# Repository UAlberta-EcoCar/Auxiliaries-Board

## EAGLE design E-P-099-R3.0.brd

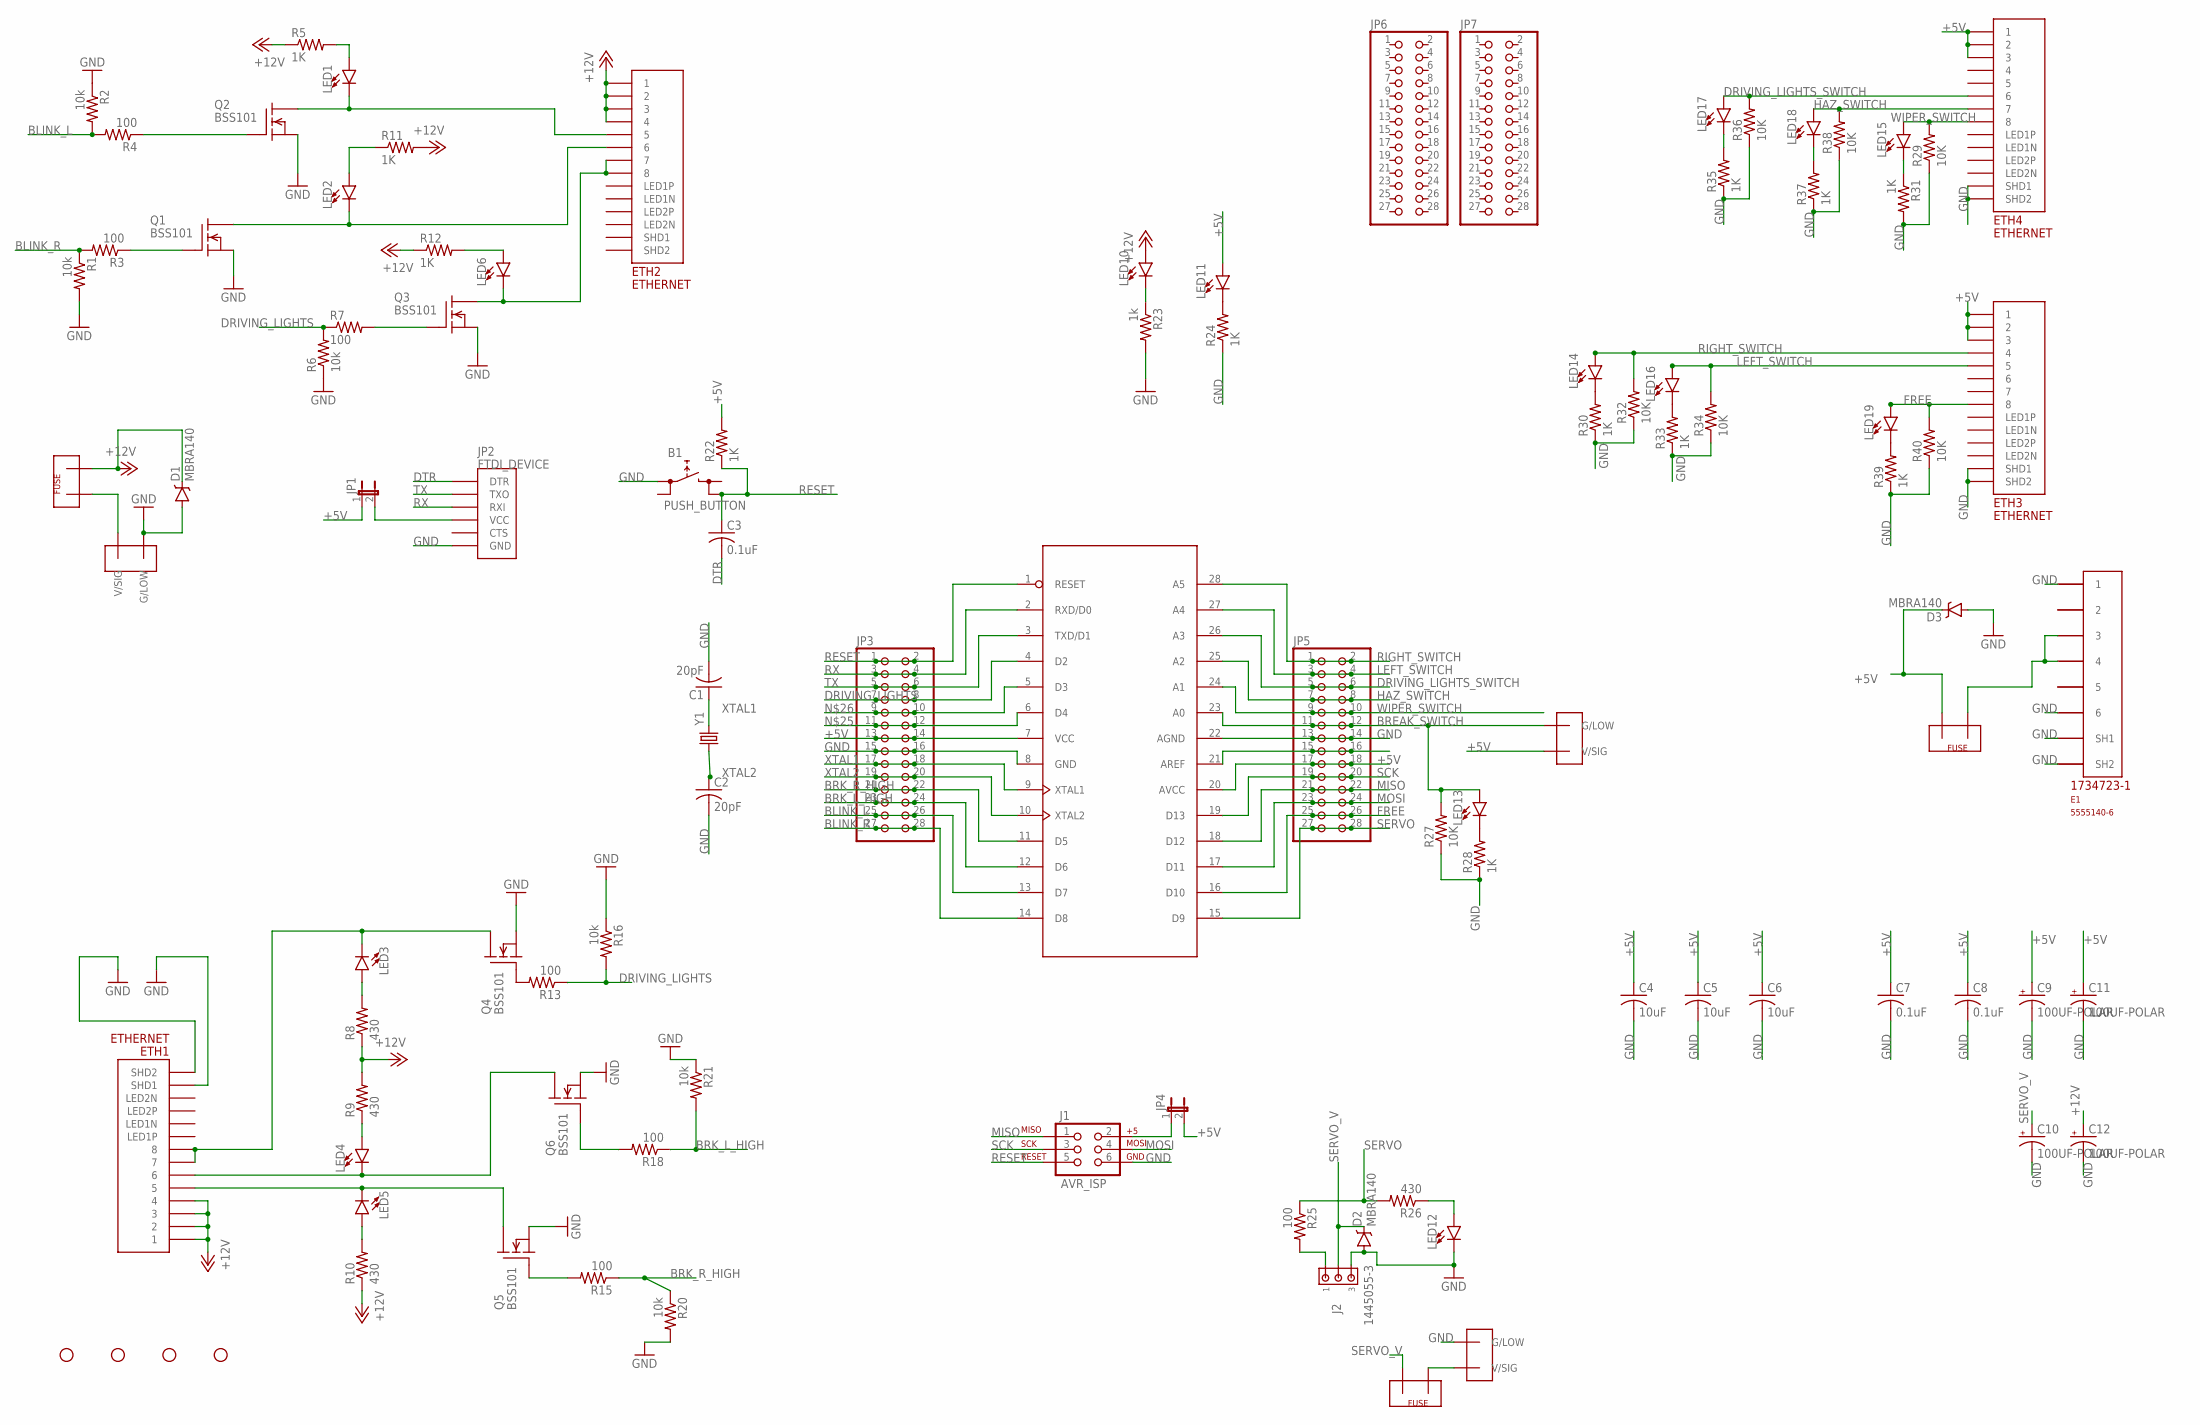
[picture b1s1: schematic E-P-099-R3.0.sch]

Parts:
AT1: ATMEGA328; DIP28-0.3IN
B1: PUSH_BUTTON; PUSHBUTTON
C1, C2: 20pF; C0805
C3, C7, C8: 0.1uF; C0805
C4, C5, C6: 10uF; C0805
C9, C10, C11, C12: 100UF-POLAR; EEU-FR1H101
D1, D2, D3: MBRA140; SMA-DIODE
E1: 5555140-6; 1734723-1_RJ11
ETH1, ETH2, ETH3, ETH4: ETHERNET; A122645-ND
F1, F2, F3: FUSEMINI-BLADE; MINI-BLADE-FUSE
J1: AVR_ISP; 2X3
J2: 1445055-3
JP1, JP4: JP1E; JP1
JP2: FTDI_DEVICE; FTDI_DEVICE_SIDE
JP3, JP5, JP6, JP7: PINHD-2X14; 2X14
LED1, LED2, LED3, LED4, LED5, LED6, LED10, LED11, LED12, LED13, LED14, LED15, LED16, LED17, LED18, LED19: LED0603; LED-0603
Q1, Q2, Q3, Q4, Q5, Q6: BSS101; TO92
R1, R2, R6, R16, R20, R21: 10k; 0805
R3, R4, R7, R13, R15, R18, R25: 100; 0805
R5, R11, R12, R22, R24, R28, R30, R31, R33, R35, R37, R39: 1K; 0805
R8, R9, R10, R26: 430; 0805
R23: 1k; 0805
R27, R29, R32, R34, R36, R38, R40: 10K; R0805
STANDOFF1, STANDOFF2, STANDOFF3, STANDOFF4: STAND-OFF
TE1, TE3: TE770966; 2X1-MATE-N-LOCK
TE2: SERVO_PWR; 2X1-MATE-N-LOCK
Y1: CRYSTALHC49US; HC49US

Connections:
+5V: AT1.7 (VCC), AT1.20 (AVCC), C4.1, C5.1, C6.1, C7.1, C8.1, C9.P (+), C11.P (+), D3.C, ETH3.P$1 (1), ETH3.P$2 (2), ETH3.P$3 (3), ETH4.P$1 (1), ETH4.P$2 (2), ETH4.P$3 (3), F3.OUT, JP1.1, JP3.13, JP3.14, JP4.2, JP5.17, JP5.18, LED11.A, R22.2, TE3.CIRCUIT1 (V/SIG)
+12V: C12.P (+), D1.C, ETH1.P$1 (1), ETH1.P$2 (2), ETH1.P$3 (3), ETH1.P$4 (4), ETH2.P$1 (1), ETH2.P$2 (2), ETH2.P$3 (3), ETH2.P$4 (4), F1.OUT, LED10.A, R5.1, R8.1, R9.2, R10.1, R11.2, R12.1
BLINK_L: AT1.13 (D7), JP3.25, JP3.26, R2.2, R4.2
BLINK_R: AT1.14 (D8), JP3.27, JP3.28, R1.1, R3.2
BREAK_SWITCH: AT1.23 (A0), JP5.11, JP5.12, LED13.A, R27.2, TE3.CIRCUIT2 (G/LOW)
BRK_L_HIGH: AT1.12 (D6), JP3.23, JP3.24, R18.1, R21.2
BRK_R_HIGH: AT1.11 (D5), JP3.21, JP3.22, R15.1, R20.1
DRIVING_LIGHTS: AT1.4 (D2), JP3.7, JP3.8, R6.2, R7.1, R13.1, R16.2
DRIVING_LIGHTS_SWITCH: AT1.26 (A3), ETH4.P$6 (6), JP5.5, JP5.6, LED17.A, R36.2
DTR: C3.2, JP2.P$1 (DTR)
FREE: AT1.16 (D10), ETH3.P$8 (8), JP5.25, JP5.26, LED19.A, R40.2
GND: AT1.8 (GND), AT1.22 (AGND), B1.L1 (L), C1.2, C2.2, C4.2, C5.2, C6.2, C7.2, C8.2, C9.G (-), C10.G (-), C11.G (-), C12.G (-), D1.A, D2.A, D3.A, E1.1, E1.6, E1.SH1, E1.SH2, ETH1.P$13 (SHD1), ETH1.P$14 (SHD2), ETH3.P$13 (SHD1), ETH3.P$14 (SHD2), ETH4.P$13 (SHD1), ETH4.P$14 (SHD2), J1.6, J2.3, JP2.P$6 (GND), JP3.15, JP3.16, JP5.13, JP5.14, LED12.C, Q1.1 (S), Q2.1 (S), Q3.1 (S), Q4.1 (S), Q5.1 (S), Q6.1 (S), R1.2, R2.1, R6.1, R16.1, R20.2, R21.1, R23.2, R24.1, R27.1, R28.1, R29.1, R30.1, R31.2, R32.1, R33.1, R34.1, R35.1, R36.1, R37.1, R38.1, R39.1, R40.1, TE1.CIRCUIT2 (G/LOW), TE2.CIRCUIT2 (G/LOW)
HAZ_SWITCH: AT1.25 (A2), ETH4.P$7 (7), JP5.7, JP5.8, LED18.A, R38.2
LEFT_SWITCH: AT1.27 (A4), ETH3.P$5 (5), JP5.3, JP5.4, LED16.A, R34.2
MISO: AT1.18 (D12), J1.1, JP5.21, JP5.22
MOSI: AT1.17 (D11), J1.4, JP5.23, JP5.24
unnamed: LED14.C, R30.2
unnamed: LED17.C, R35.2
unnamed: LED16.C, R33.2
unnamed: ETH1.P$7 (7), ETH1.P$8 (8), LED3.C, Q4.3 (D)
unnamed: ETH1.P$6 (6), LED4.C, Q6.3 (D)
unnamed: E1.3, E1.4, F3.IN
unnamed: ETH1.P$5 (5), LED5.C, Q5.3 (D)
unnamed: Q4.2 (G), R13.2
unnamed: JP1.2, JP2.P$4 (VCC)
unnamed: LED19.C, R39.2
unnamed: LED13.C, R28.2
unnamed: LED12.A, R26.1
unnamed: J2.1, R25.2
unnamed: Q5.2 (G), R15.2
unnamed: Q6.2 (G), R18.2
unnamed: LED10.C, R23.1
unnamed: Q2.2 (G), R4.1
unnamed: LED5.A, R10.2
unnamed: LED11.C, R24.2
unnamed: ETH2.P$7 (7), ETH2.P$8 (8), LED6.C, Q3.3 (D)
unnamed: ETH2.P$6 (6), LED2.C, Q1.3 (D)
unnamed: ETH2.P$5 (5), LED1.C, Q2.3 (D)
unnamed: LED4.A, R9.1
unnamed: AT1.6 (D4), JP3.11, JP3.12
unnamed: AT1.5 (D3), JP3.9, JP3.10
unnamed: LED3.A, R8.2
unnamed: LED15.C, R31.1
unnamed: F2.IN, TE2.CIRCUIT1 (V/SIG)
unnamed: LED1.A, R5.2
unnamed: Q1.2 (G), R3.1
unnamed: LED2.A, R11.1
unnamed: Q3.2 (G), R7.2
unnamed: LED6.A, R12.2
unnamed: J1.2, JP4.1
unnamed: LED18.C, R37.2
unnamed: F1.IN, TE1.CIRCUIT1 (V/SIG)
unnamed: AT1.21 (AREF), JP5.15, JP5.16
RESET: AT1.1 (RESET), B1.R2 (R), C3.1, J1.5, JP3.1, JP3.2, R22.1
RIGHT_SWITCH: AT1.28 (A5), ETH3.P$4 (4), JP5.1, JP5.2, LED14.A, R32.2
RX: AT1.2 (RXD/D0), JP2.P$3 (RXI), JP3.3, JP3.4
SCK: AT1.19 (D13), J1.3, JP5.19, JP5.20
SERVO: AT1.15 (D9), JP5.27, JP5.28, R25.1, R26.2
SERVO_V: C10.P (+), D2.C, F2.OUT, J2.2
TX: AT1.3 (TXD/D1), JP2.P$2 (TXO), JP3.5, JP3.6
WIPER_SWITCH: AT1.24 (A1), ETH4.P$8 (8), JP5.9, JP5.10, LED15.A, R29.2
XTAL1: AT1.9 (XTAL1), C1.1, JP3.17, JP3.18, Y1.2
XTAL2: AT1.10 (XTAL2), C2.1, JP3.19, JP3.20, Y1.1

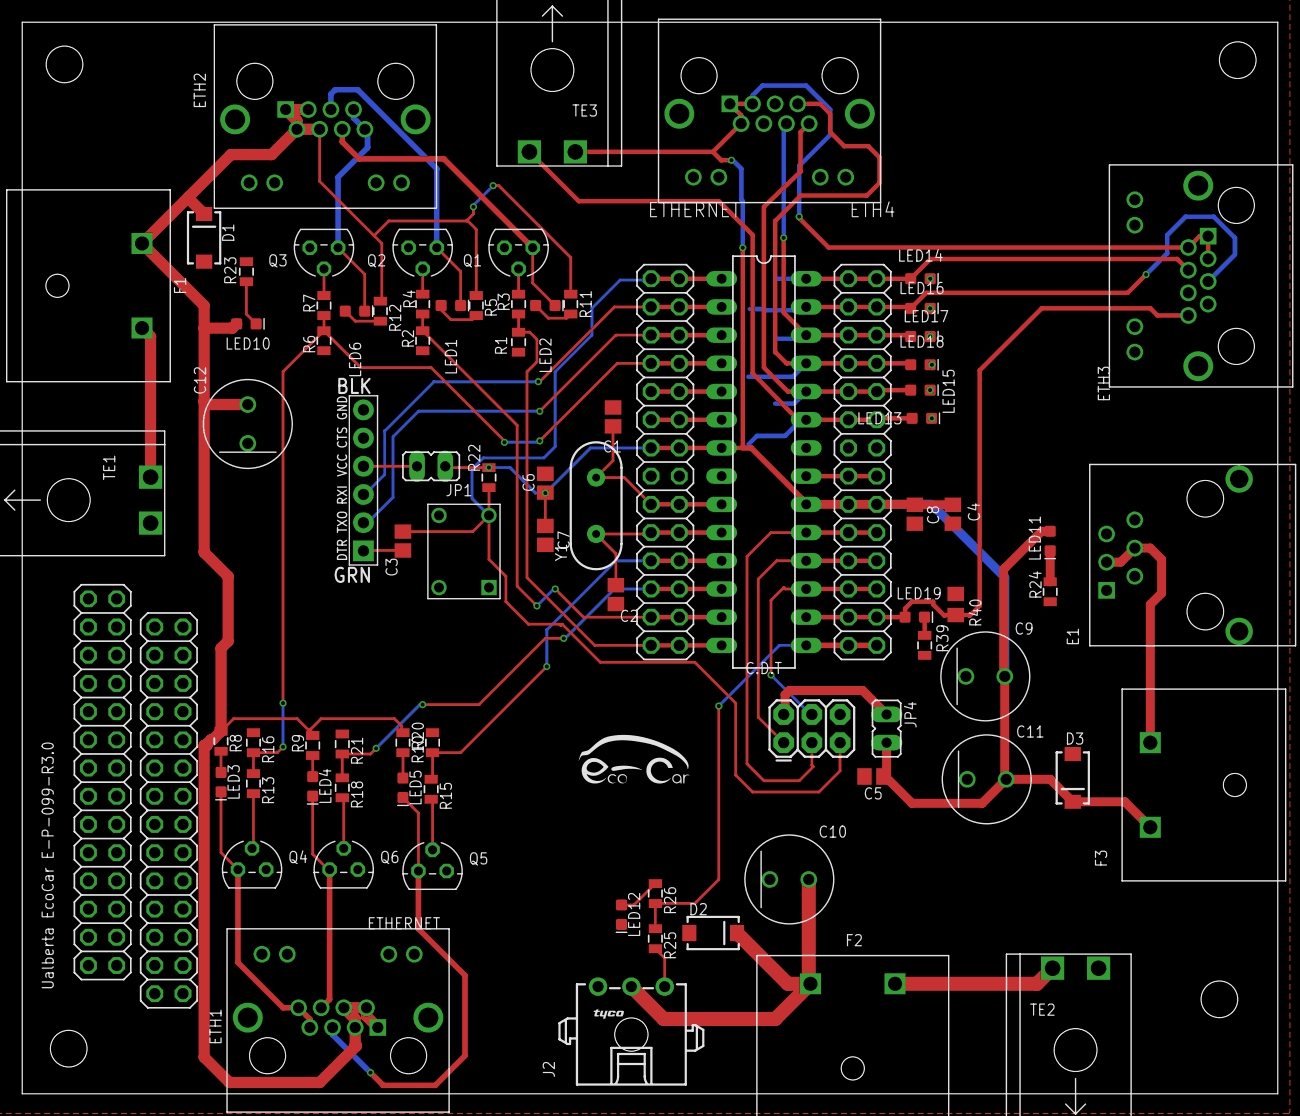
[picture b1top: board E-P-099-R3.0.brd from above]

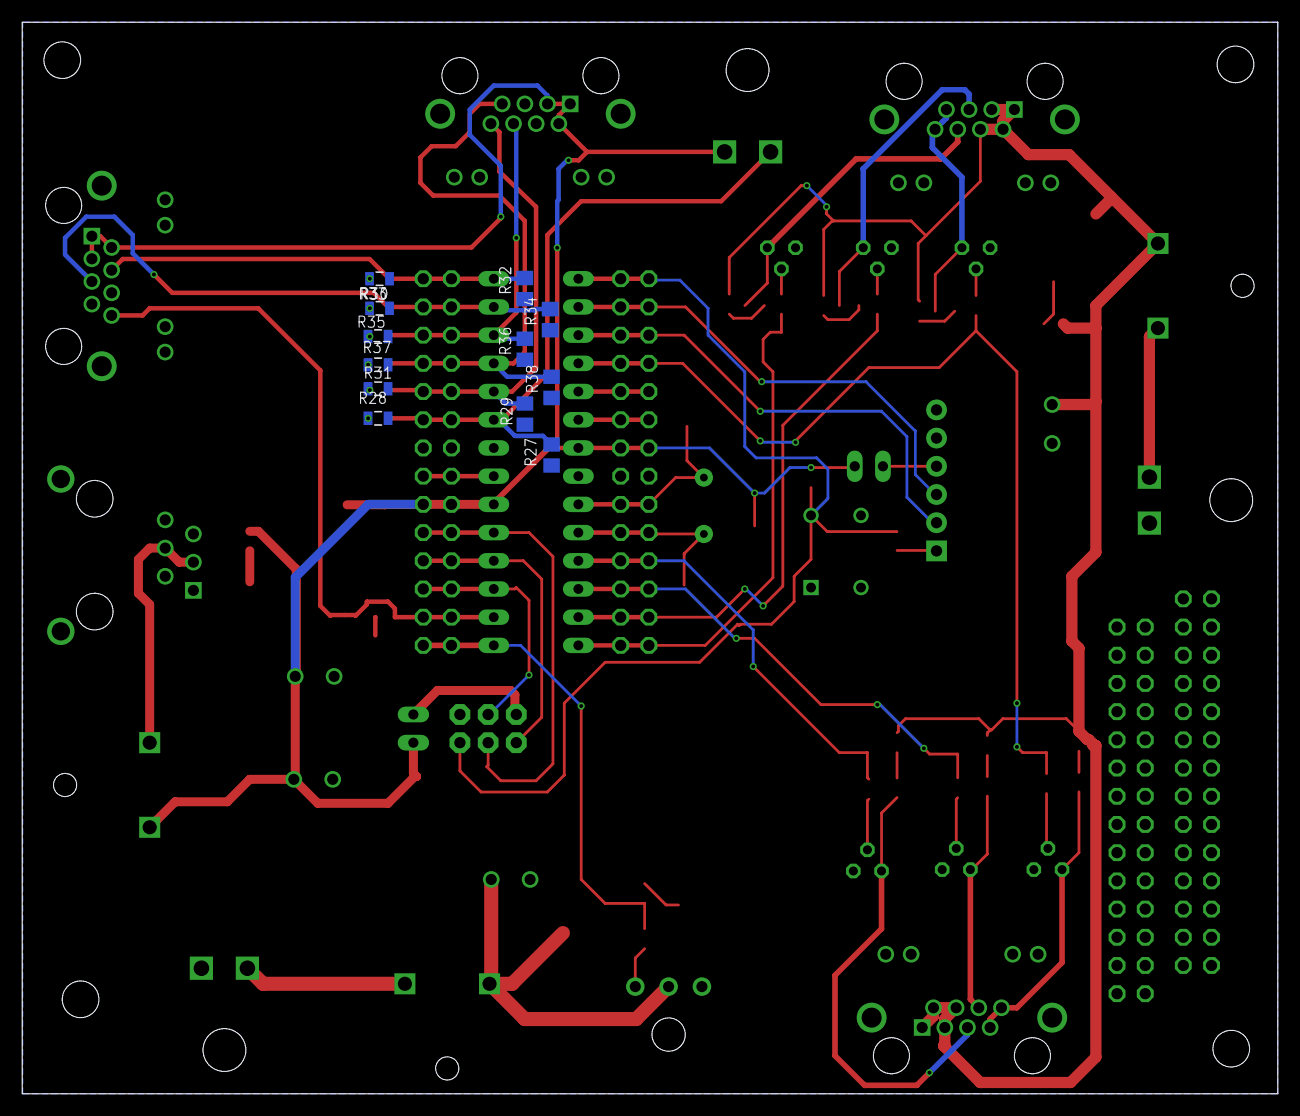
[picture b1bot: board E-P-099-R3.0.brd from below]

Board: 2 copper layers, 113.1 x 96.5 mm, 101 parts (12 on the bottom side), 63 nets.

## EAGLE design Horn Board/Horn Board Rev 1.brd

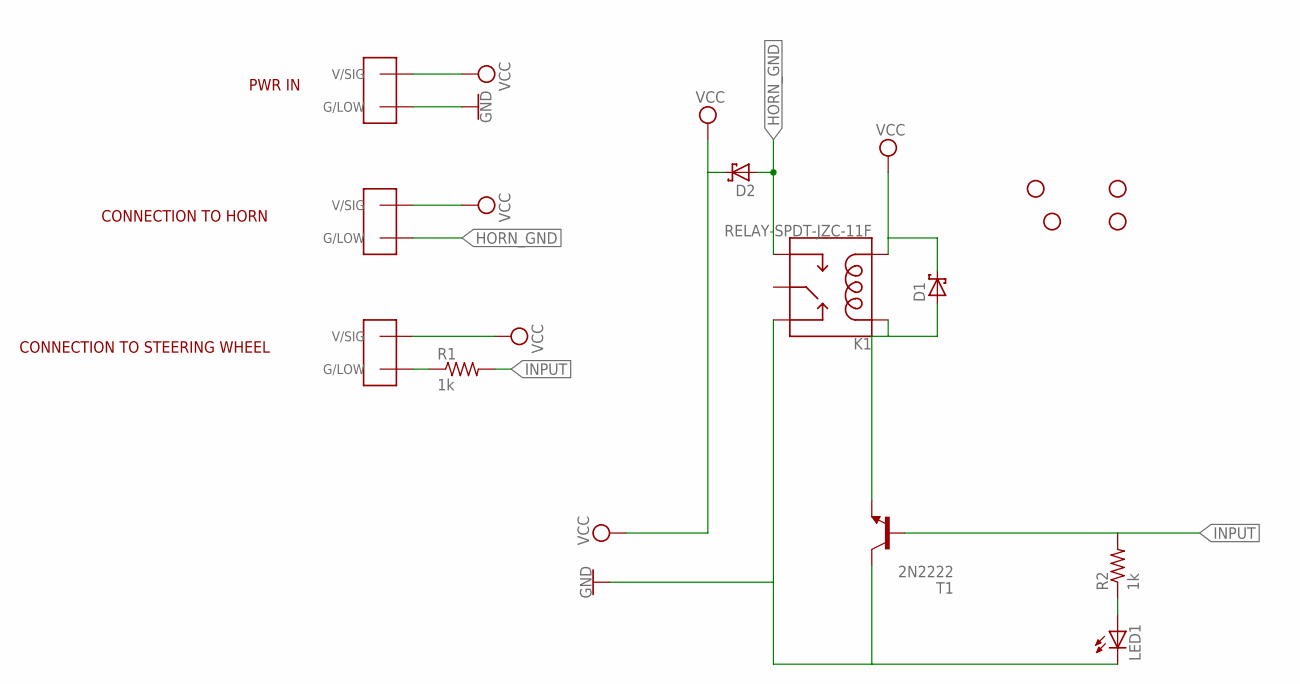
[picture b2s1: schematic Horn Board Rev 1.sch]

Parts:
D1, D2: SCHOTTKY-DIODEAG; AG
H1, H2, H3, H4: STAND-OFF
K1: RELAY-SPDT-JZC-11F; RELAY-JZC
LED1: LED; SMARTLED-TTW
R1, R2: 1k; 0204V
T1: 2N2222; TO92-EBC-OVAL
U$1, U$2, U$8: TE770966; 2X1-MATE-N-LOCK

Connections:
GND: K1.2 (NC), LED1.C@1 (C), T1.C, U$8.CIRCUIT2 (G/LOW)
HORN_GND: D2.A, K1.3 (NO), U$1.CIRCUIT2 (G/LOW)
INPUT: R1.2, R2.2, T1.B
unnamed: R1.1, U$2.CIRCUIT2 (G/LOW)
unnamed: D1.A, K1.5 (COIL1), T1.E
unnamed: LED1.A@1 (A), R2.1
VCC: D1.C, D2.C, K1.1 (COIL2), U$1.CIRCUIT1 (V/SIG), U$2.CIRCUIT1 (V/SIG), U$8.CIRCUIT1 (V/SIG)

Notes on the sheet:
PWR IN
CONNECTION TO HORN
CONNECTION TO STEERING WHEEL

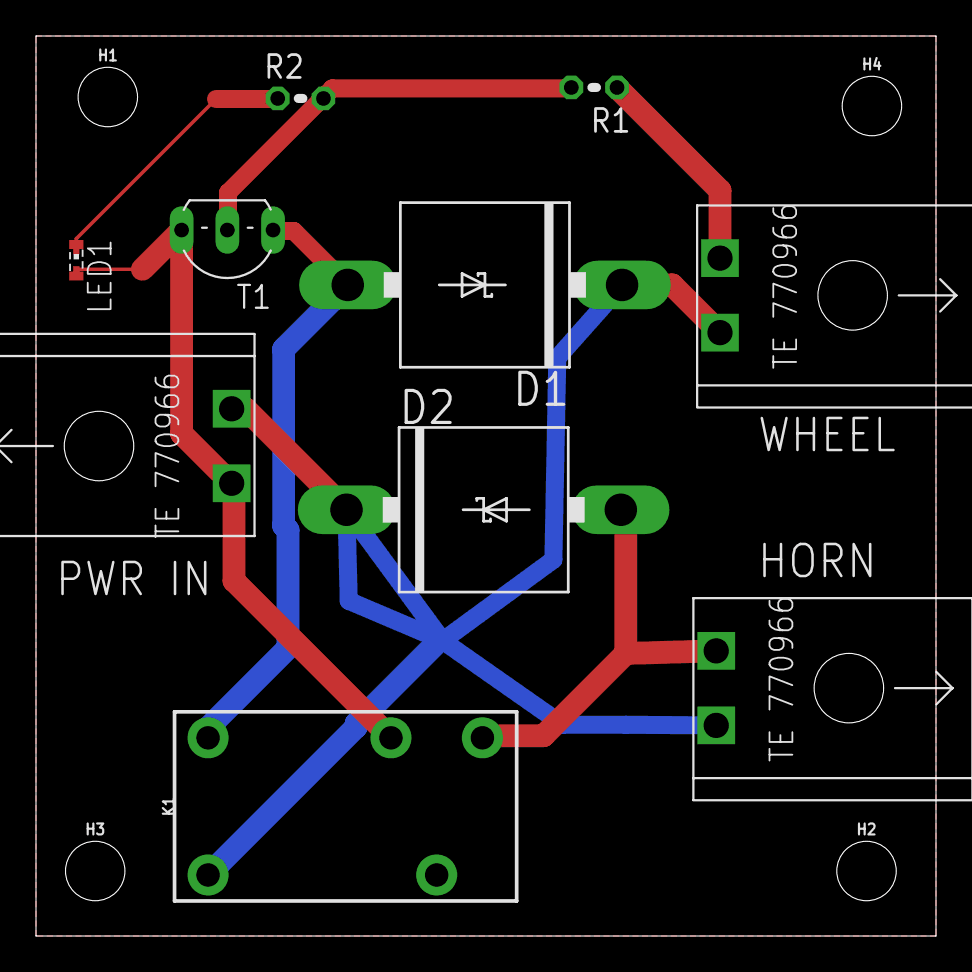
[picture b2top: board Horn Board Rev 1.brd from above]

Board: 2 copper layers, 50.0 x 50.0 mm, 14 parts (0 on the bottom side), 7 nets.

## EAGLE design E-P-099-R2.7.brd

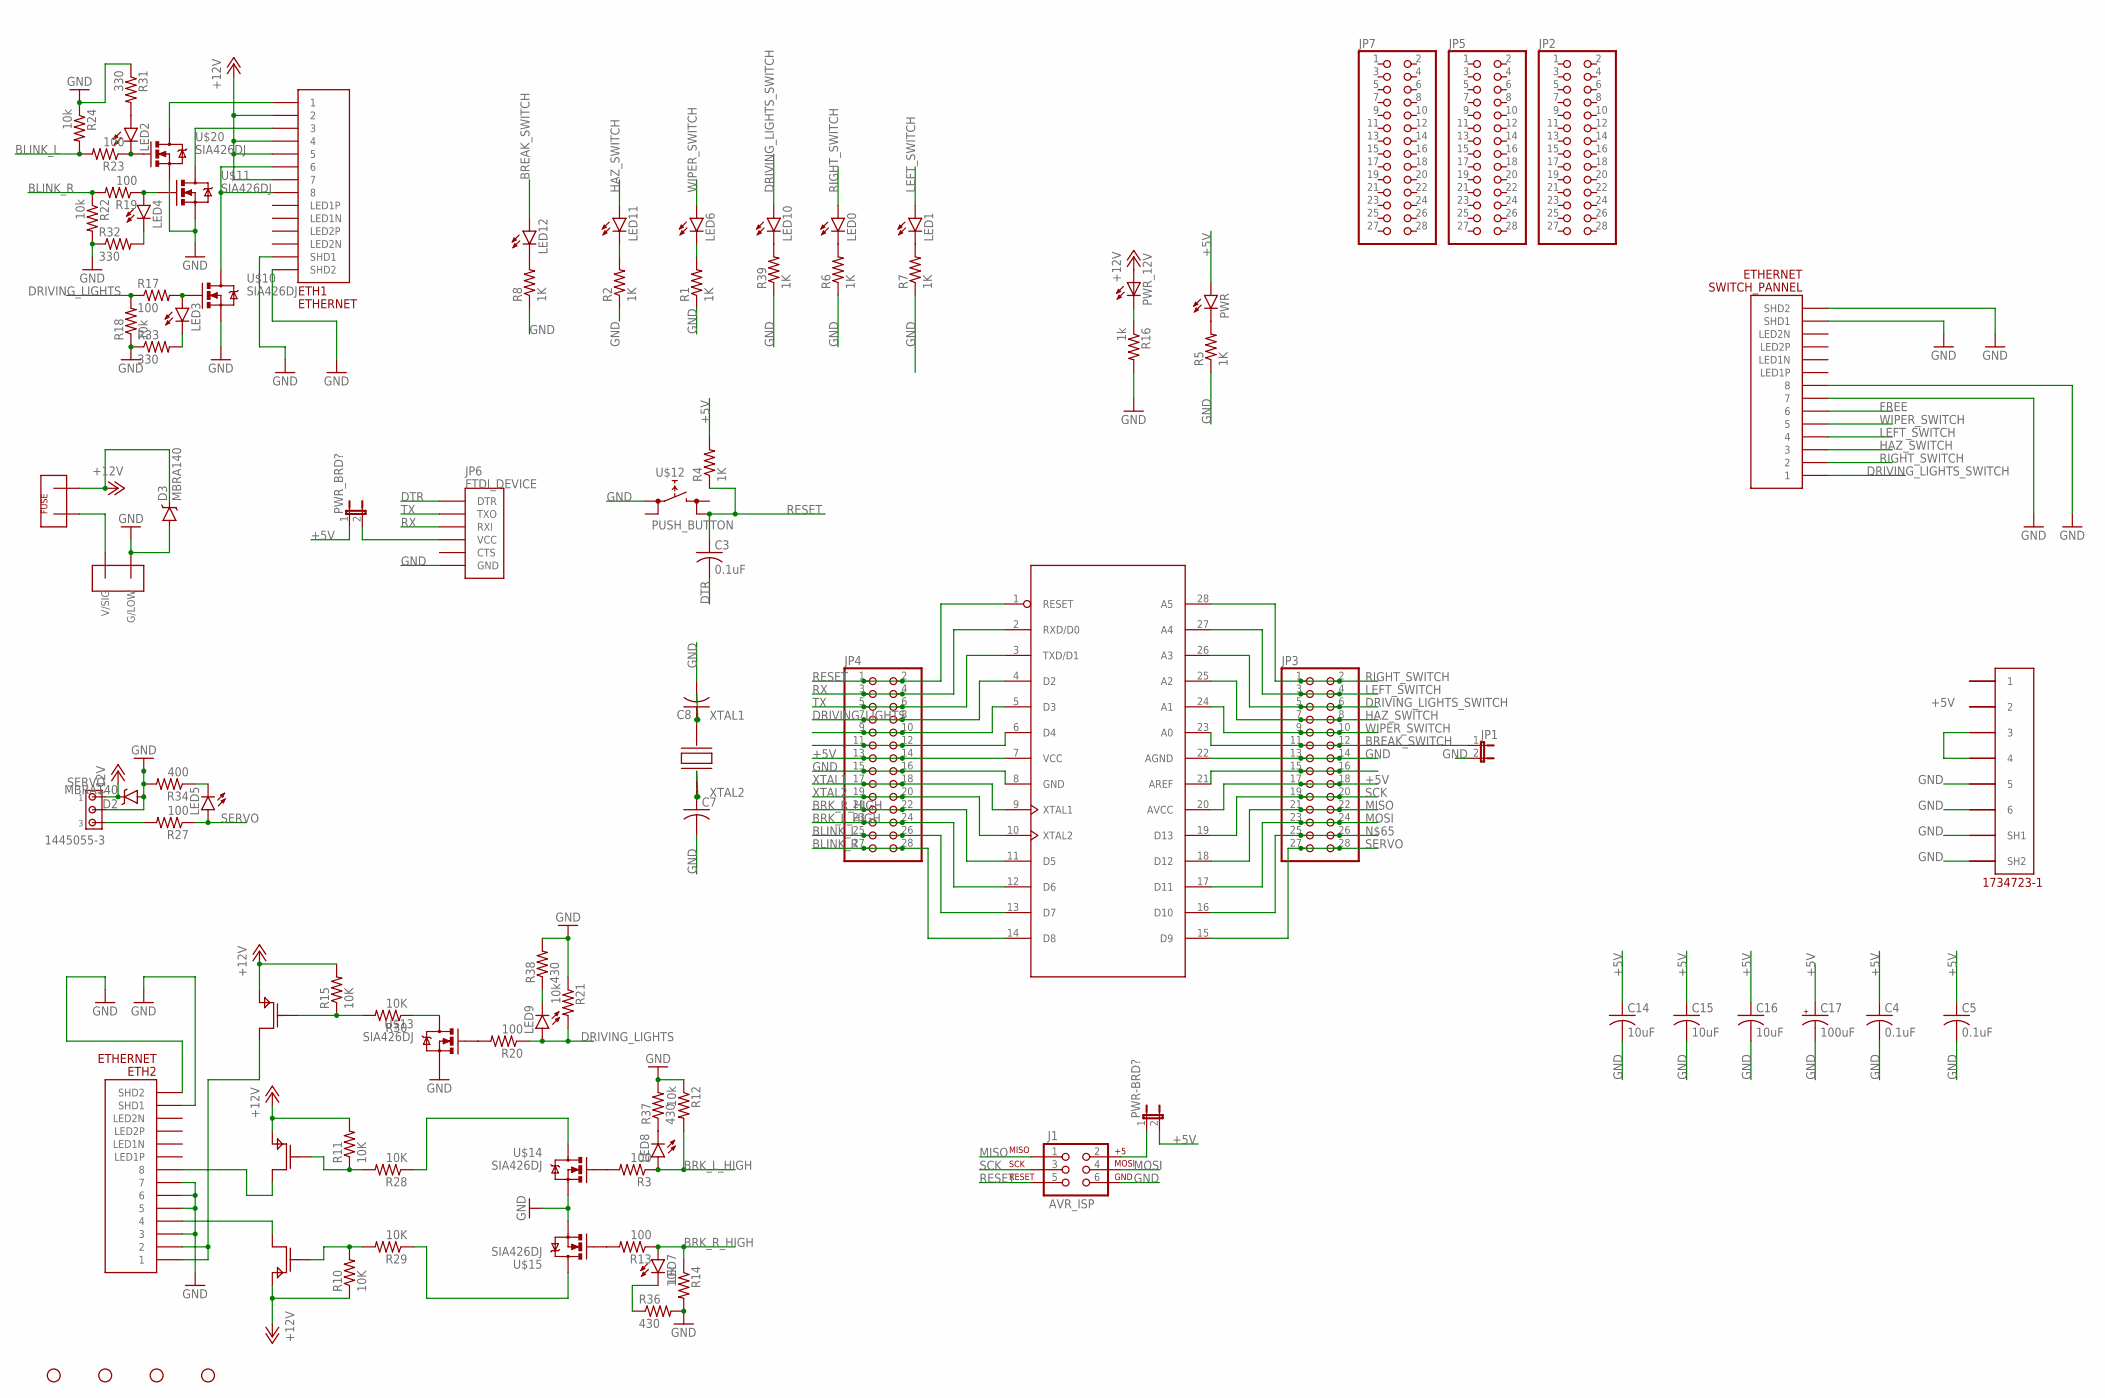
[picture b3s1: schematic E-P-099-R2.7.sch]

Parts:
5V_IN: 5555140-6; 1734723-1_RJ11
C3, C4, C5: 0.1uF; C0805
C7, C8: C-USC0805; C0805
C14, C15, C16: 10uF; C0805
C17: 100uF; PANASONIC_D
D2, D3: MBRA140; SMA-DIODE
ETH1, ETH2: ETHERNET; A122645-ND
J1: AVR_ISP; 2X3
JP1: JUMPER-2PTH; 1X02
JP2, JP3, JP4, JP5, JP7: PINHD-2X14; 2X14
JP6: FTDI_DEVICE; FTDI_DEVICE_SIDE
LED0, LED1, LED2, LED3, LED4, LED5, LED6, LED7, LED8, LED9, LED10, LED11, LED12: LED0603; LED-0603
PWR: LED0603; LED-0603
PWR-BRD?: JP1E; JP1
PWR_12V: LEDCHIPLED_1206; CHIPLED_1206
PWR_BRD?: JP1E; JP1
R1, R2, R4, R5, R6, R7, R8, R39: 1K; 0805
R3, R13, R17, R19, R20, R23, R27: 100; 0805
R10, R11, R15, R28, R29, R30: 10K; 0805
R12, R14, R18, R21, R22, R24: 10k; 0805
R16: 1k; 0805
R31, R32, R33: 330; 0805
R34: 400; 0805
R36, R37, R38: 430; 0805
SERVO: 1445055-3
STANDOFF1, STANDOFF2, STANDOFF3, STANDOFF4: STAND-OFF
SWITCH_PANNEL: ETHERNET; A122645-ND
U$3, U$5, U$6: SIA449DJ; SIA449DJ-T1-GE3CT-ND
U$4: ATMEGA328; DIP28-0.3IN
U$8: TE770966; 2X1-MATE-N-LOCK
U$9: FUSEMINI-BLADE; MINI-BLADE-FUSE
U$10, U$11, U$13, U$14, U$15, U$20: SIA426DJ; SC70-6L
U$12: PUSH_BUTTON; PUSHBUTTON
U$18: CRYSTAL; 7A_CRYSTAL

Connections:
+5V: 5V_IN.3, 5V_IN.4, C4.1, C5.1, C14.1, C15.1, C16.1, C17.+, JP3.17, JP3.18, JP4.13, JP4.14, PWR.A, PWR-BRD?.2, PWR_BRD?.1, R4.2, U$4.7 (VCC), U$4.20 (AVCC)
+12V: D2.C, D3.C, ETH1.P$2 (2), ETH1.P$4 (4), ETH1.P$5 (5), ETH1.P$7 (7), PWR_12V.A, R10.1, R11.2, R15.2, SERVO.1, U$3.P$4 (P$S), U$3.P$5 (P$S), U$5.P$4 (P$S), U$5.P$5 (P$S), U$6.P$4 (P$S), U$6.P$5 (P$S), U$9.OUT
BLINK_L: JP4.25, JP4.26, R23.2, R24.2, U$4.13 (D7)
BLINK_R: JP4.27, JP4.28, R19.2, R22.1, U$4.14 (D8)
BREAK_SWITCH: JP1.1, JP3.11, JP3.12, LED12.A, U$4.23 (A0)
BRK_L_HIGH: JP4.23, JP4.24, LED8.A, R3.1, R12.2, U$4.12 (D6)
BRK_R_HIGH: JP4.21, JP4.22, LED7.A, R13.1, R14.1, U$4.11 (D5)
DRIVING_LIGHTS: JP4.7, JP4.8, LED9.A, R17.1, R18.2, R20.1, R21.2, U$4.4 (D2)
DRIVING_LIGHTS_SWITCH: JP3.5, JP3.6, LED10.A, SWITCH_PANNEL.P$1 (1), U$4.26 (A3)
DTR: C3.2, JP6.P$1 (DTR)
FREE: SWITCH_PANNEL.P$6 (6)
GND: 5V_IN.5, 5V_IN.6, 5V_IN.SH1, 5V_IN.SH2, C4.2, C5.2, C7.2, C8.2, C14.2, C15.2, C16.2, C17.-, D2.A, D3.A, ETH1.P$13 (SHD1), ETH1.P$14 (SHD2), ETH2.P$3 (3), ETH2.P$5 (5), ETH2.P$6 (6), ETH2.P$7 (7), ETH2.P$13 (SHD1), ETH2.P$14 (SHD2), J1.6, JP1.2, JP3.13, JP3.14, JP4.15, JP4.16, JP6.P$6 (GND), R1.1, R2.1, R5.1, R6.1, R7.1, R8.1, R12.1, R14.2, R16.2, R18.1, R21.1, R22.2, R24.1, R31.1, R32.1, R33.1, R34.2, R36.2, R37.2, R38.2, R39.1, SERVO.2, SWITCH_PANNEL.P$7 (7), SWITCH_PANNEL.P$8 (8), SWITCH_PANNEL.P$13 (SHD1), SWITCH_PANNEL.P$14 (SHD2), U$4.8 (GND), U$4.22 (AGND), U$8.CIRCUIT2 (G/LOW), U$10.S@0 (S), U$10.S@1 (S), U$11.S@0 (S), U$11.S@1 (S), U$12.L1 (L), U$13.S@0 (S), U$13.S@1 (S), U$14.S@0 (S), U$14.S@1 (S), U$15.S@0 (S), U$15.S@1 (S), U$20.S@0 (S), U$20.S@1 (S)
HAZ_SWITCH: JP3.7, JP3.8, LED11.A, SWITCH_PANNEL.P$3 (3), U$4.25 (A2)
LEFT_SWITCH: JP3.3, JP3.4, LED1.A, SWITCH_PANNEL.P$4 (4), U$4.27 (A4)
MISO: J1.1, JP3.21, JP3.22, U$4.18 (D12)
MOSI: J1.4, JP3.23, JP3.24, U$4.17 (D11)
unnamed: LED12.C, R8.2
unnamed: LED6.C, R1.2
unnamed: LED11.C, R2.2
unnamed: ETH2.P$4 (4), U$6.P$1 (P$D)
unnamed: ETH2.P$8 (8), U$5.P$1 (P$D)
unnamed: R13.2, U$15.G
unnamed: R20.2, U$13.G
unnamed: JP6.P$4 (VCC), PWR_BRD?.2
unnamed: LED0.C, R6.2
unnamed: LED1.C, R7.2
unnamed: ETH2.P$1 (1), ETH2.P$2 (2), U$3.P$1 (P$D)
unnamed: R11.1, R28.2, U$5.P$6 (P$G)
unnamed: PWR_12V.C, R16.1
unnamed: LED2.C, R23.1, U$20.G
unnamed: PWR.C, R5.2
unnamed: ETH1.P$1 (1), U$20.D
unnamed: R3.2, U$14.G
unnamed: R15.1, R30.2, U$3.P$6 (P$G)
unnamed: ETH1.P$3 (3), U$11.D
unnamed: JP4.11, JP4.12, U$4.6 (D4)
unnamed: JP4.9, JP4.10, U$4.5 (D3)
unnamed: ETH1.P$6 (6), ETH1.P$8 (8), U$10.D
unnamed: LED4.C, R32.2
unnamed: R10.2, R29.2, U$6.P$6 (P$G)
unnamed: LED4.A, R19.1, U$11.G
unnamed: R30.1, U$13.D
unnamed: LED3.A, R17.2, U$10.G
unnamed: R27.2, SERVO.3
unnamed: J1.2, PWR-BRD?.1
unnamed: LED3.C, R33.2
unnamed: LED5.C, R34.1
unnamed: LED7.C, R36.1
unnamed: LED8.C, R37.1
unnamed: R28.1, U$14.D
unnamed: LED9.C, R38.1
unnamed: R29.1, U$15.D
unnamed: LED10.C, R39.2
unnamed: U$8.CIRCUIT1 (V/SIG), U$9.IN
unnamed: LED2.A, R31.2
unnamed: JP3.15, JP3.16, U$4.21 (AREF)
unnamed: JP3.25, JP3.26, U$4.16 (D10)
RESET: C3.1, J1.5, JP4.1, JP4.2, R4.1, U$4.1 (RESET), U$12.R2 (R)
RIGHT_SWITCH: JP3.1, JP3.2, LED0.A, SWITCH_PANNEL.P$2 (2), U$4.28 (A5)
RX: JP4.3, JP4.4, JP6.P$3 (RXI), U$4.2 (RXD/D0)
SCK: J1.3, JP3.19, JP3.20, U$4.19 (D13)
SERVO: JP3.27, JP3.28, LED5.A, R27.1, U$4.15 (D9)
TX: JP4.5, JP4.6, JP6.P$2 (TXO), U$4.3 (TXD/D1)
WIPER_SWITCH: JP3.9, JP3.10, LED6.A, SWITCH_PANNEL.P$5 (5), U$4.24 (A1)
XTAL1: C8.1, JP4.17, JP4.18, U$4.9 (XTAL1), U$18.P$2
XTAL2: C7.1, JP4.19, JP4.20, U$4.10 (XTAL2), U$18.P$1

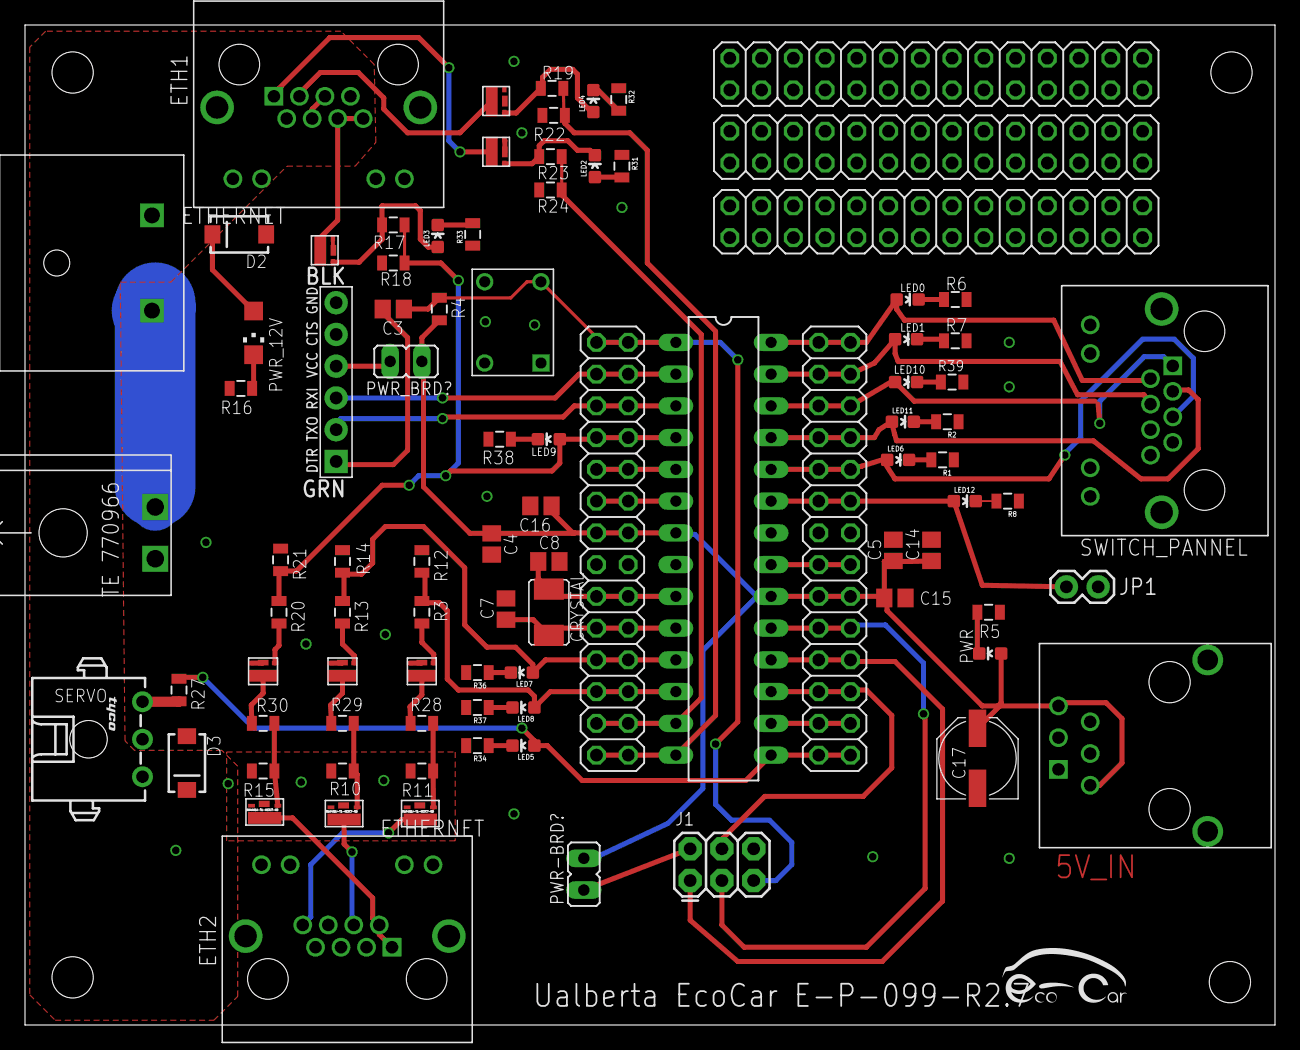
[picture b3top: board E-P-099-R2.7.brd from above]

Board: 2 copper layers, 100.0 x 80.0 mm, 94 parts (0 on the bottom side), 65 nets.

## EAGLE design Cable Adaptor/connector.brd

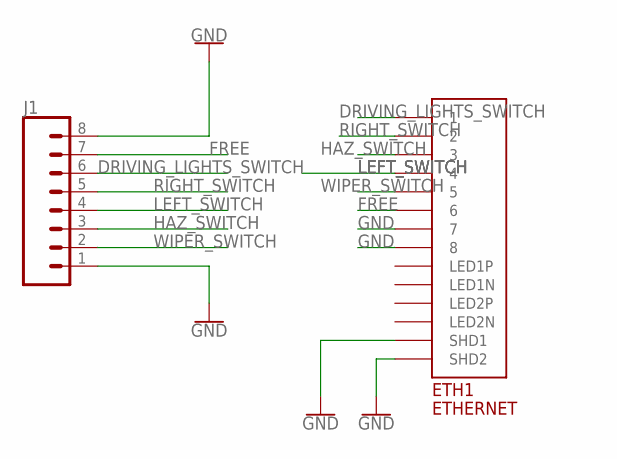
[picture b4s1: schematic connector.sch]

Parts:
ETH1: ETHERNET; A122645-ND
J1: CONN_08FEMALE_LOCK; 1X08_FEMALE_LOCK

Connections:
DRIVING_LIGHTS_SWITCH: ETH1.P$1 (1), J1.6
FREE: ETH1.P$6 (6), J1.7
GND: ETH1.P$7 (7), ETH1.P$8 (8), ETH1.P$13 (SHD1), ETH1.P$14 (SHD2), J1.1, J1.8
HAZ_SWITCH: ETH1.P$3 (3), J1.3
LEFT_SWITCH: ETH1.P$4 (4), J1.4
RIGHT_SWITCH: ETH1.P$2 (2), J1.5
WIPER_SWITCH: ETH1.P$5 (5), J1.2

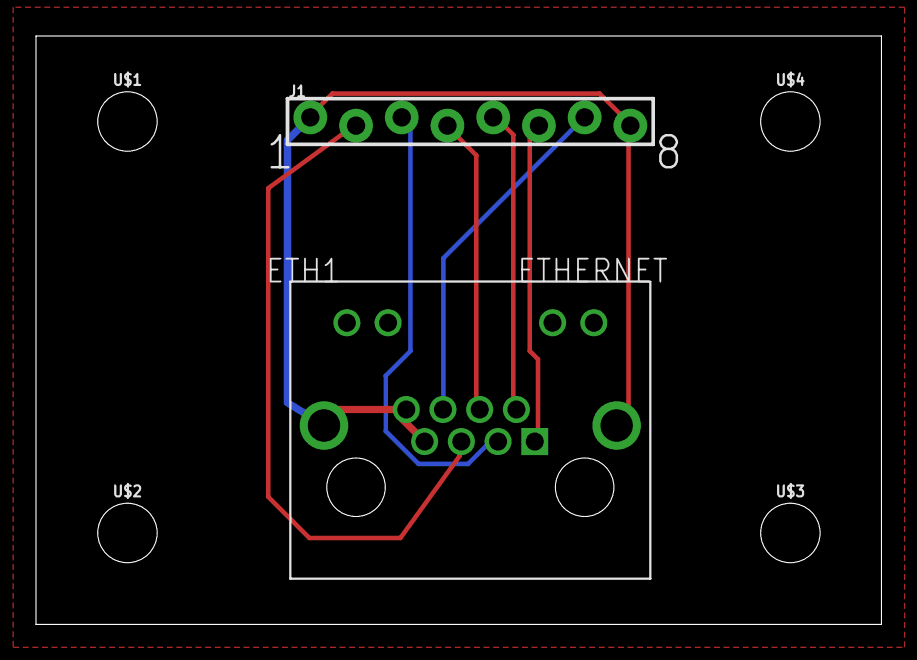
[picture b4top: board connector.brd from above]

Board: 2 copper layers, 47.0 x 32.7 mm, 6 parts (0 on the bottom side), 7 nets.

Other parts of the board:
U$1, U$2, U$3, U$4: STAND-OFF

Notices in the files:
parts and their libraries:
SparkFun-Connectors: Licensing: Creative Commons ShareAlike 4.0 International - https://creativecommons.org/licenses/by-sa/4.0
SparkFun: Licensing: CC v3.0 Share-Alike You are welcome to use this library for commercial purposes.
